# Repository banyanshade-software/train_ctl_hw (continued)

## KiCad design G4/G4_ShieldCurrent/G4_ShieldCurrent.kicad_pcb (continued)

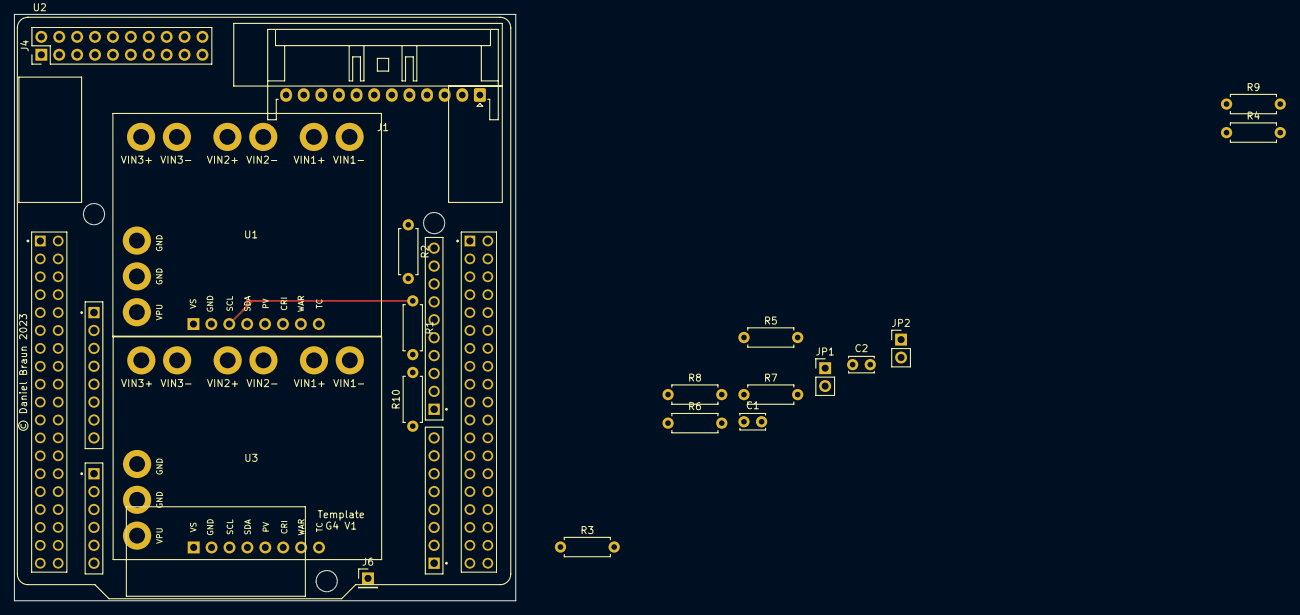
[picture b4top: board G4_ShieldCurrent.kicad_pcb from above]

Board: 2 copper layers, 71.1 x 83.2 mm, 20 parts (0 on the bottom side), 27 nets.

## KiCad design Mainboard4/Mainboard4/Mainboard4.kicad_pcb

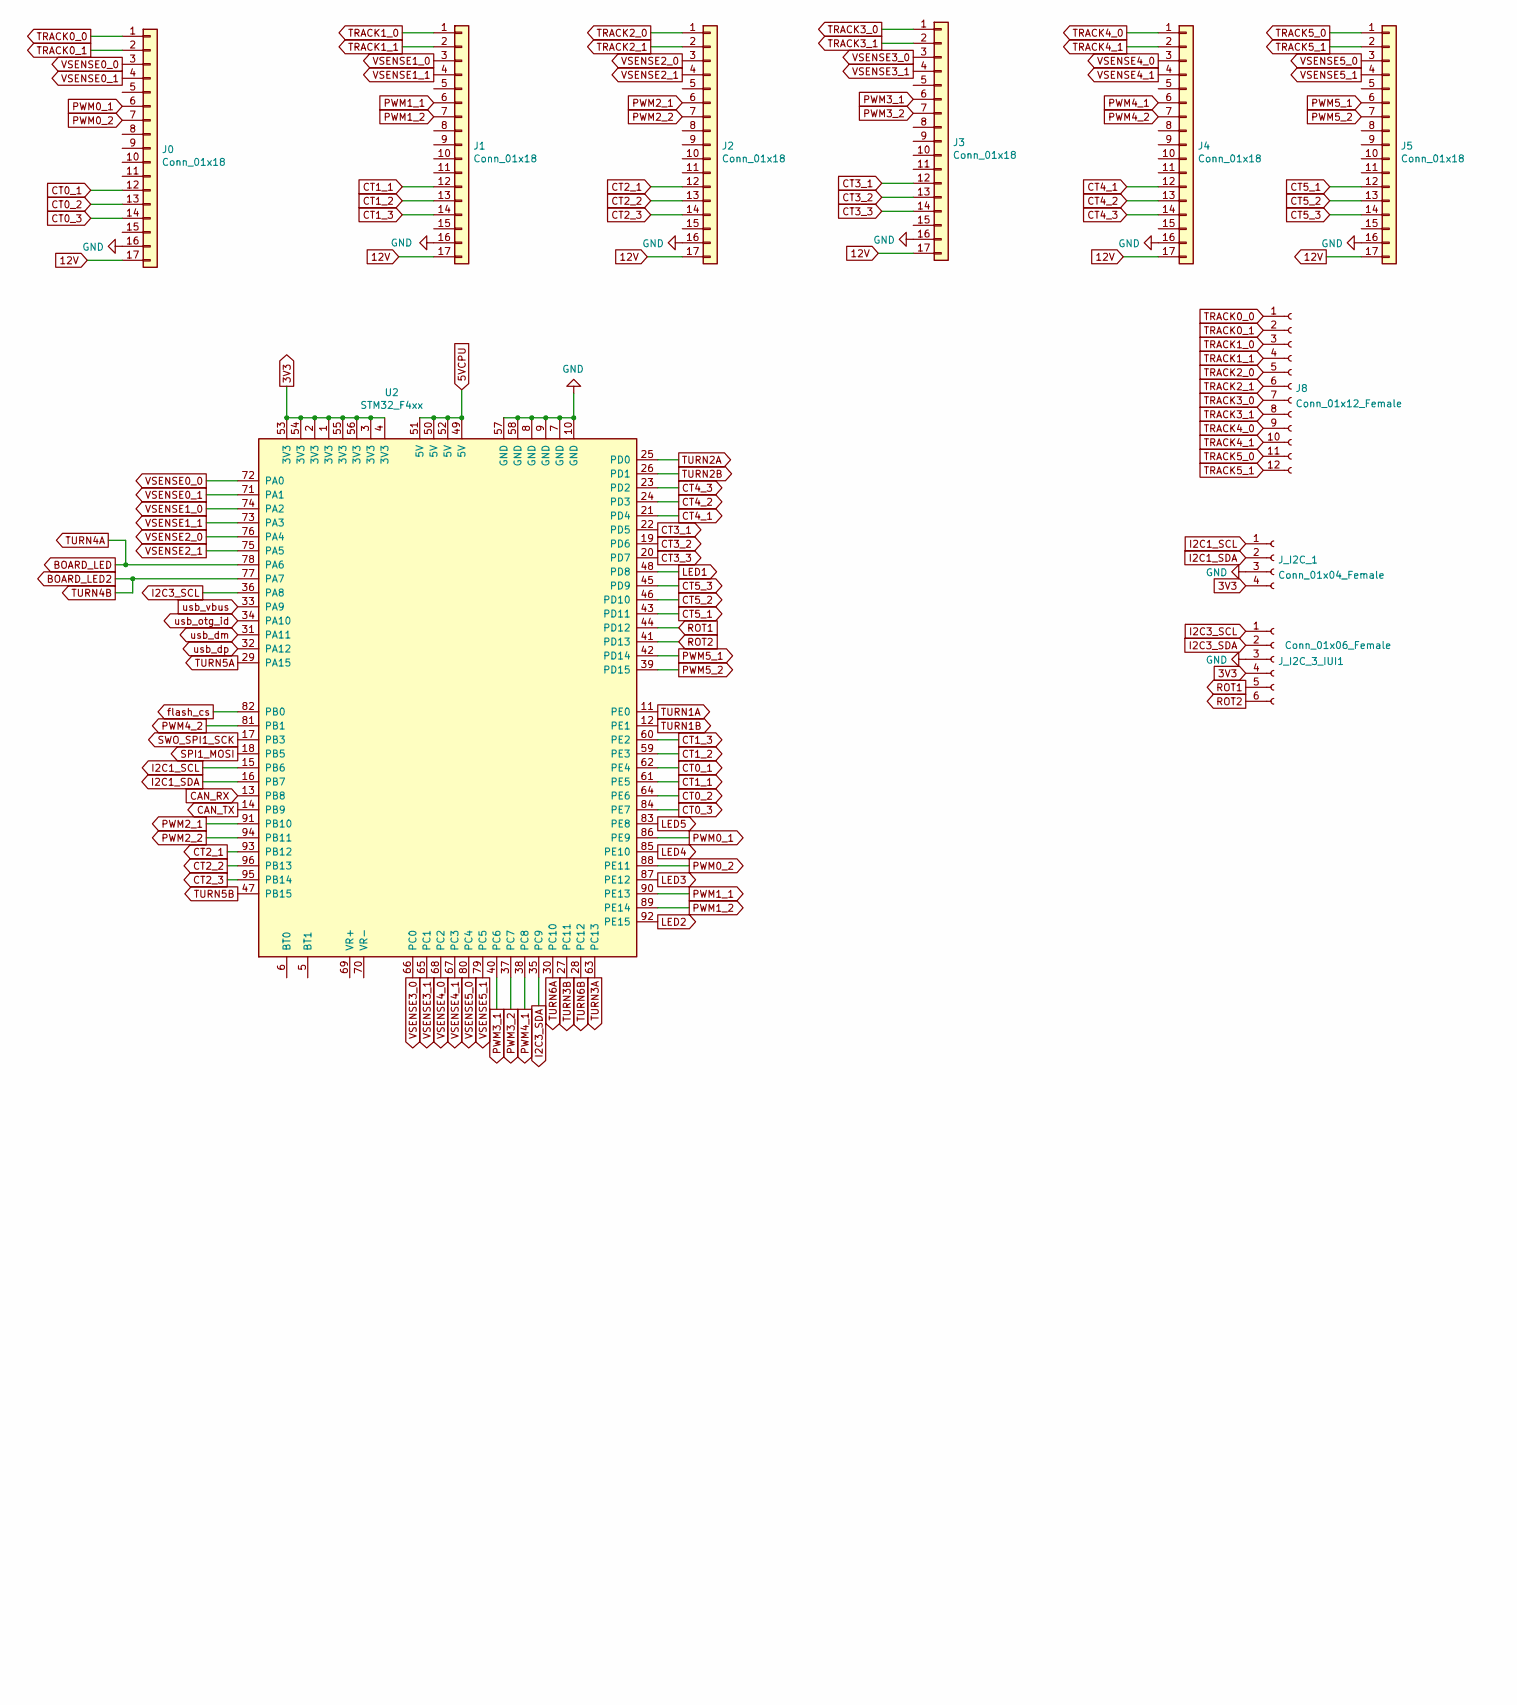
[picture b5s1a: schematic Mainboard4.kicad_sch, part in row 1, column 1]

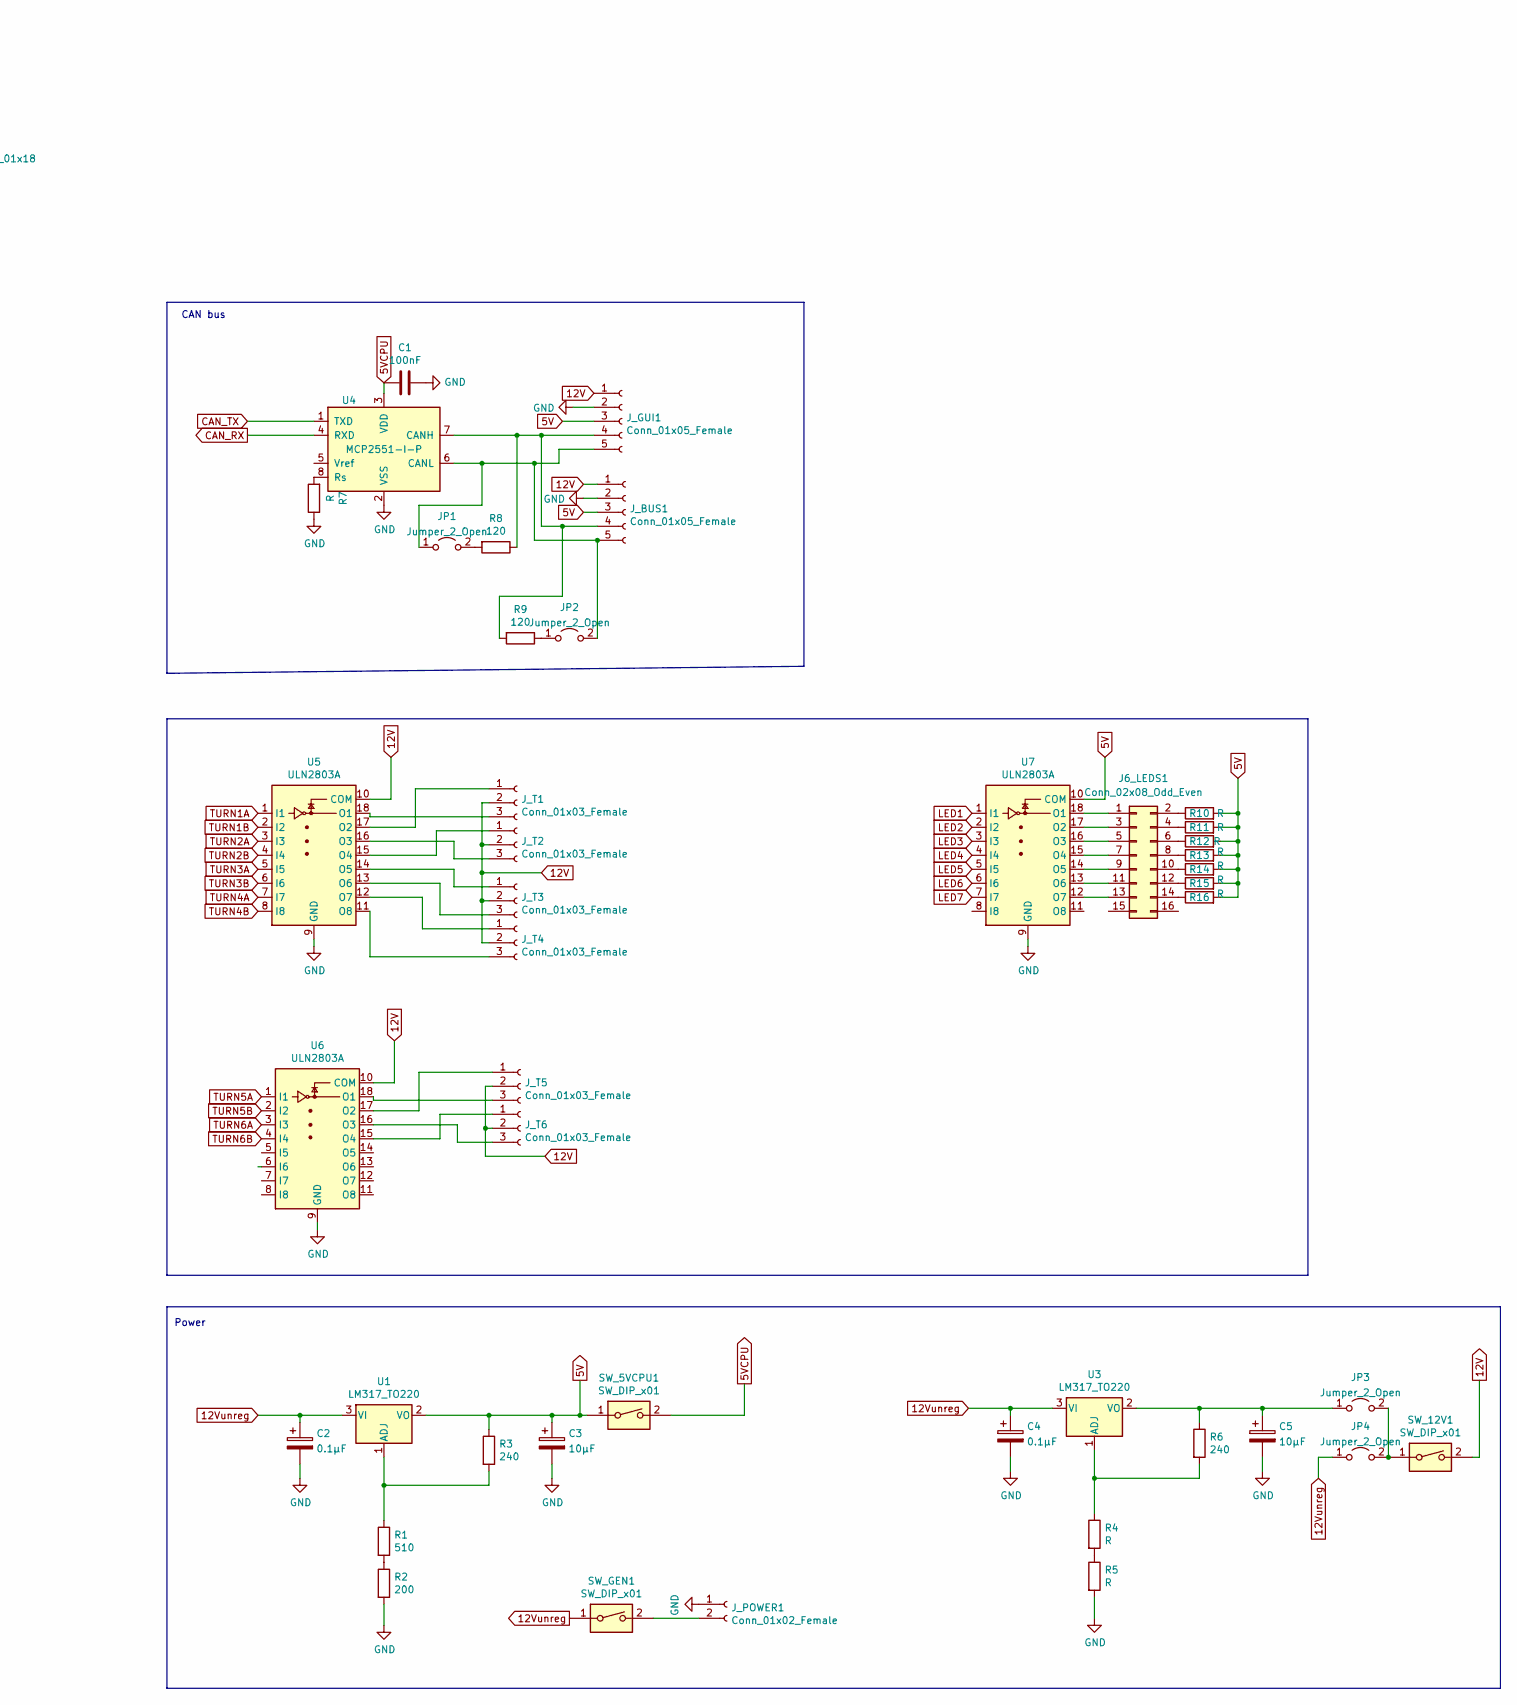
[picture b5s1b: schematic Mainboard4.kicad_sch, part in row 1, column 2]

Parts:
C1: 100nF; C_Disc_D3.4mm_W2.1mm_P2.50mm
C2, C4: 0.1µF; CP_Radial_Tantal_D5.0mm_P2.50mm
C3, C5: 10µF; CP_Radial_Tantal_D5.0mm_P2.50mm
J0, J1, J2, J3, J4, J5: Conn_01x18; PinHeader_1x17_P2.54mm_Vertical
J6_LEDS1: Conn_02x08_Odd_Even; PinHeader_2x08_P2.54mm_Vertical
J8: Conn_01x12_Female; PinHeader_1x12_P2.54mm_Vertical
JP1, JP2, JP3, JP4: Jumper_2_Open; PinHeader_1x02_P2.54mm_Vertical
J_BUS1: Conn_01x05_Female; PinHeader_1x05_P2.54mm_Vertical
J_GUI1: Conn_01x05_Female; PinHeader_1x05_P2.54mm_Vertical
J_I2C_1: Conn_01x04_Female; PinHeader_1x04_P2.54mm_Vertical
J_I2C_3_IUI1: Conn_01x06_Female; PinHeader_1x06_P2.54mm_Vertical
J_POWER1: Conn_01x02_Female; PinHeader_1x02_P2.54mm_Vertical
J_T1, J_T2, J_T3, J_T4, J_T5, J_T6: Conn_01x03_Female; PinHeader_1x03_P2.54mm_Vertical
R1: 510; R_Axial_DIN0207_L6.3mm_D2.5mm_P7.62mm_Horizontal
R2: 200; R_Axial_DIN0207_L6.3mm_D2.5mm_P7.62mm_Horizontal
R3, R6: 240; R_Axial_DIN0207_L6.3mm_D2.5mm_P7.62mm_Horizontal
R4, R5, R7, R10, R11, R12, R13, R14, R15, R16: R; R_Axial_DIN0207_L6.3mm_D2.5mm_P7.62mm_Horizontal
R8, R9: 120; R_Axial_DIN0207_L6.3mm_D2.5mm_P7.62mm_Horizontal
SW_5VCPU1, SW_12V1: SW_DIP_x01; PinHeader_1x02_P2.54mm_Vertical
SW_GEN1: SW_DIP_x01; PinHeader_1x02_P2.54mm_Vertical
U1, U3: LM317_TO220; TO-220-3_Vertical
U2: STM32_F4xx; STM32_F4XXrev
U4: MCP2551-I-P; DIP-8_W7.62mm
U5, U6, U7: ULN2803A; DIP-18_W7.62mm

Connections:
3V3: J_I2C_1.4, J_I2C_3_IUI1.4, U2.1 (3V3), U2.2 (3V3), U2.3 (3V3), U2.4 (3V3), U2.53 (3V3), U2.54 (3V3), U2.55 (3V3), U2.56 (3V3)
5V: C3.1, J_BUS1.3, J_GUI1.3, R3.1, R10.2, R11.2, R12.2, R13.2, R14.2, R15.2, R16.2, SW_5VCPU1.1, U1.2 (VO), U7.10 (COM)
5VCPU: C1.2, SW_5VCPU1.2, U2.49 (5V), U2.50 (5V), U2.51 (5V), U2.52 (5V), U4.3 (VDD)
12V: J0.17, J1.17, J2.17, J3.17, J4.17, J5.17, J_BUS1.1, J_GUI1.1, J_T1.2, J_T2.2, J_T3.2, J_T4.2, J_T5.2, J_T6.2, SW_12V1.2, U5.10 (COM), U6.10 (COM)
12Vunreg: C2.1, C4.1, JP4.1 (A), SW_GEN1.1, U1.3 (VI), U3.3 (VI)
BOARD_LED: U2.78 (PA6), U5.7 (I7)
BOARD_LED2: U2.77 (PA7), U5.8 (I8)
CAN_RX: U2.13 (PB8), U4.4 (RXD)
CAN_TX: U2.14 (PB9), U4.1 (TXD)
CT0_1: J0.12, U2.62 (PE4)
CT0_2: J0.13, U2.64 (PE6)
CT0_3: J0.14, U2.84 (PE7)
CT1_1: J1.12, U2.61 (PE5)
CT1_2: J1.13, U2.59 (PE3)
CT1_3: J1.14, U2.60 (PE2)
CT2_1: J2.12, U2.93 (PB12)
CT2_2: J2.13, U2.96 (PB13)
CT2_3: J2.14, U2.95 (PB14)
CT3_1: J3.12, U2.22 (PD5)
CT3_2: J3.13, U2.19 (PD6)
CT3_3: J3.14, U2.20 (PD7)
CT4_1: J4.12, U2.21 (PD4)
CT4_2: J4.13, U2.24 (PD3)
CT4_3: J4.14, U2.23 (PD2)
CT5_1: J5.12, U2.43 (PD11)
CT5_2: J5.13, U2.46 (PD10)
CT5_3: J5.14, U2.45 (PD9)
GND: C1.1, C2.2, C3.2, C4.2, C5.2, J0.16, J1.16, J2.16, J3.16, J4.16, J5.16, J_BUS1.2, J_GUI1.2, J_I2C_1.3, J_I2C_3_IUI1.3, J_POWER1.1, R2.2, R5.2, R7.1, U2.7 (GND), U2.8 (GND), U2.9 (GND), U2.10 (GND), U2.57 (GND), U2.58 (GND), U4.2 (VSS), U5.9 (GND), U6.9 (GND), U7.9 (GND)
I2C1_SCL: J_I2C_1.1, U2.15 (PB6)
I2C1_SDA: J_I2C_1.2, U2.16 (PB7)
I2C3_SCL: J_I2C_3_IUI1.1, U2.36 (PA8)
I2C3_SDA: J_I2C_3_IUI1.2, U2.35 (PC9)
LED1: U2.48 (PD8), U7.1 (I1)
LED2: U2.92 (PE15), U7.2 (I2)
LED3: U2.87 (PE12), U7.3 (I3)
LED4: U2.85 (PE10), U7.4 (I4)
LED5: U2.83 (PE8), U7.5 (I5)
LED6: U7.6 (I6)
LED7: U7.7 (I7)
unnamed: C5.1, JP3.1 (A), R6.1, U3.2 (VO)
unnamed: J6_LEDS1.1, U7.18 (O1)
unnamed: J6_LEDS1.2, R10.1
unnamed: J6_LEDS1.3, U7.17 (O2)
unnamed: J6_LEDS1.4, R11.1
unnamed: J6_LEDS1.5, U7.16 (O3)
unnamed: J6_LEDS1.6, R12.1
unnamed: J6_LEDS1.7, U7.15 (O4)
unnamed: J6_LEDS1.8, R13.1
unnamed: J6_LEDS1.9, U7.14 (O5)
unnamed: J6_LEDS1.10, R14.1
unnamed: J6_LEDS1.11, U7.13 (O6)
unnamed: J6_LEDS1.12, R15.1
unnamed: J6_LEDS1.13, U7.12 (O7)
unnamed: J6_LEDS1.14, R16.1
unnamed: JP1.1 (A), JP2.2 (B), J_BUS1.5, J_GUI1.5, U4.6 (CANL)
unnamed: JP1.2 (B), R8.2
unnamed: JP2.1 (A), R9.1
unnamed: JP3.2 (B), JP4.2 (B), SW_12V1.1
unnamed: J_BUS1.4, J_GUI1.4, R8.1, R9.2, U4.7 (CANH)
unnamed: J_POWER1.2, SW_GEN1.2
unnamed: J_T1.1, U5.17 (O2)
unnamed: J_T1.3, U5.18 (O1)
unnamed: J_T2.1, U5.15 (O4)
unnamed: J_T2.3, U5.16 (O3)
unnamed: J_T3.1, U5.14 (O5)
unnamed: J_T3.3, U5.13 (O6)
unnamed: J_T4.1, U5.12 (O7)
unnamed: J_T4.3, U5.11 (O8)
unnamed: J_T5.1, U6.17 (O2)
unnamed: J_T5.3, U6.18 (O1)
unnamed: J_T6.1, U6.15 (O4)
unnamed: J_T6.3, U6.16 (O3)
unnamed: R1.1, R3.2, U1.1 (ADJ)
unnamed: R1.2, R2.1
unnamed: R4.1, R6.2, U3.1 (ADJ)
unnamed: R4.2, R5.1
unnamed: R7.2, U4.8 (Rs)
PWM0_1: J0.6, U2.86 (PE9)
PWM0_2: J0.7, U2.88 (PE11)
PWM1_1: J1.6, U2.90 (PE13)
PWM1_2: J1.7, U2.89 (PE14)
PWM2_1: J2.6, U2.91 (PB10)
PWM2_2: J2.7, U2.94 (PB11)
PWM3_1: J3.6, U2.40 (PC6)
PWM3_2: J3.7, U2.37 (PC7)
PWM4_1: J4.6, U2.38 (PC8)
PWM4_2: J4.7, U2.81 (PB1)
PWM5_1: J5.6, U2.42 (PD14)
PWM5_2: J5.7, U2.39 (PD15)
ROT1: J_I2C_3_IUI1.5, U2.44 (PD12)
ROT2: J_I2C_3_IUI1.6, U2.41 (PD13)
SPI1_MOSI: U2.18 (PB5)
SWO_SPI1_SCK: U2.17 (PB3)
TRACK0_0: J0.1, J8.1
TRACK0_1: J0.2, J8.2
TRACK1_0: J1.1, J8.3
TRACK1_1: J1.2, J8.4
TRACK2_0: J2.1, J8.5
TRACK2_1: J2.2, J8.6
TRACK3_0: J3.1, J8.7
TRACK3_1: J3.2, J8.8
TRACK4_0: J4.1, J8.9
TRACK4_1: J4.2, J8.10
TRACK5_0: J5.1, J8.11
TRACK5_1: J5.2, J8.12
TURN1A: U2.11 (PE0), U5.1 (I1)
TURN1B: U2.12 (PE1), U5.2 (I2)
TURN2A: U2.25 (PD0), U5.3 (I3)
TURN2B: U2.26 (PD1), U5.4 (I4)
TURN3A: U2.63 (PC13), U5.5 (I5)
TURN3B: U2.27 (PC11), U5.6 (I6)
TURN5A: U2.29 (PA15), U6.1 (I1)
TURN5B: U2.47 (PB15), U6.2 (I2)
TURN6A: U2.30 (PC10), U6.3 (I3)
TURN6B: U2.28 (PC12), U6.4 (I4)
VSENSE0_0: J0.3, U2.72 (PA0)
VSENSE0_1: J0.4, U2.71 (PA1)
VSENSE1_0: J1.3, U2.74 (PA2)
VSENSE1_1: J1.4, U2.73 (PA3)
VSENSE2_0: J2.3, U2.76 (PA4)
VSENSE2_1: J2.4, U2.75 (PA5)
VSENSE3_0: J3.3, U2.66 (PC0)
VSENSE3_1: J3.4, U2.65 (PC1)
VSENSE4_0: J4.3, U2.68 (PC2)
VSENSE4_1: J4.4, U2.67 (PC3)
VSENSE5_0: J5.3, U2.80 (PC4)
VSENSE5_1: J5.4, U2.79 (PC5)
flash_cs: U2.82 (PB0)
usb_dm: U2.31 (PA11)
usb_dp: U2.32 (PA12)
usb_otg_id: U2.34 (PA10)
usb_vbus: U2.33 (PA9)

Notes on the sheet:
CAN bus
Power

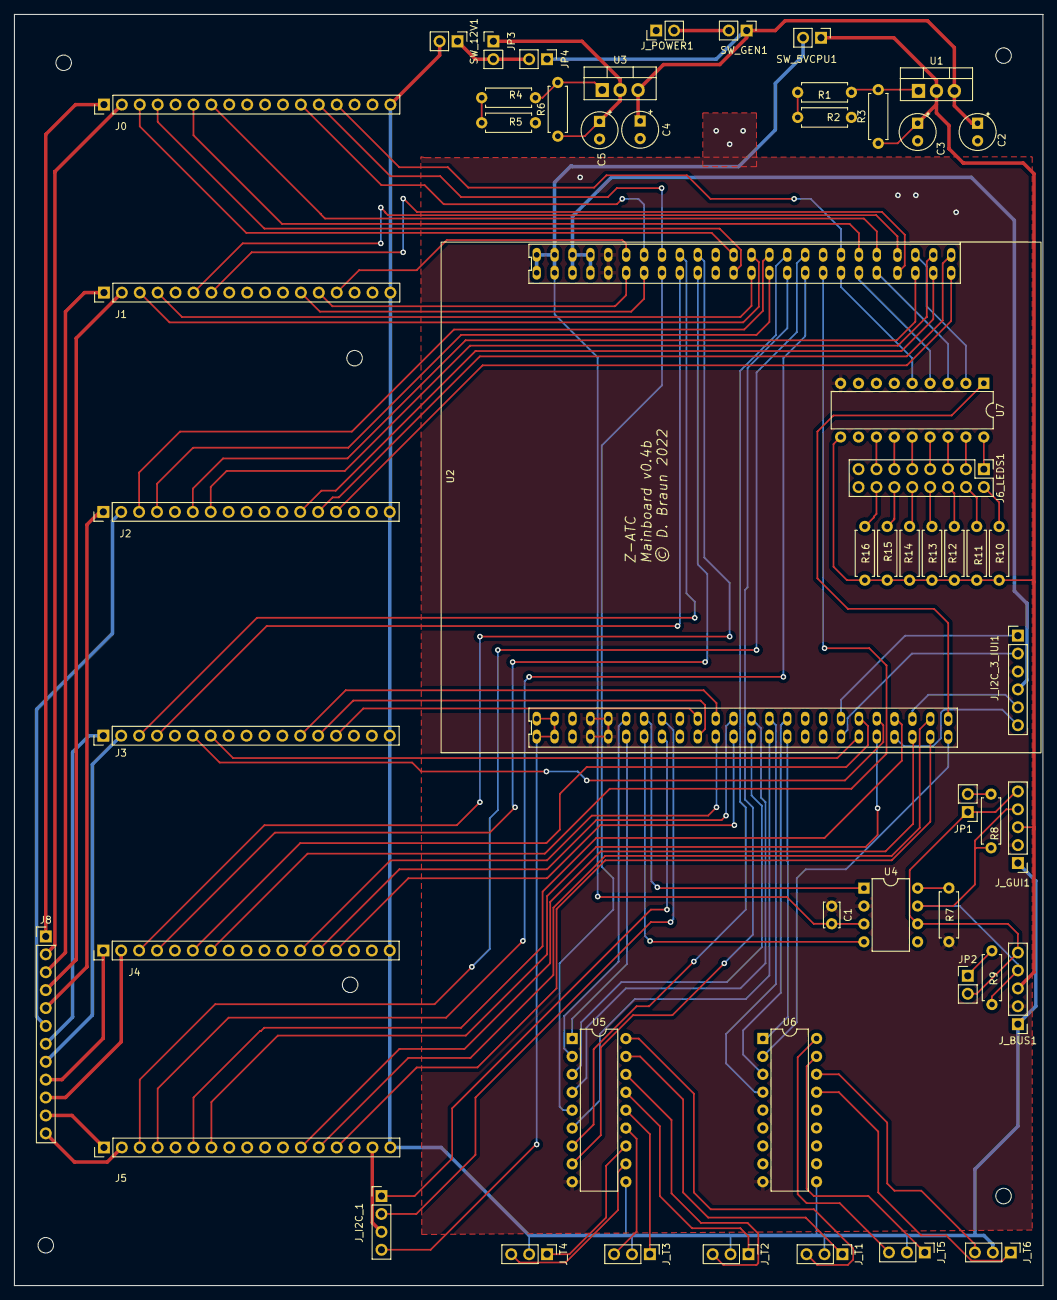
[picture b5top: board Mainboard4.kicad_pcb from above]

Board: 2 copper layers, 145.9 x 180.3 mm, 54 parts (0 on the bottom side), 123 nets.

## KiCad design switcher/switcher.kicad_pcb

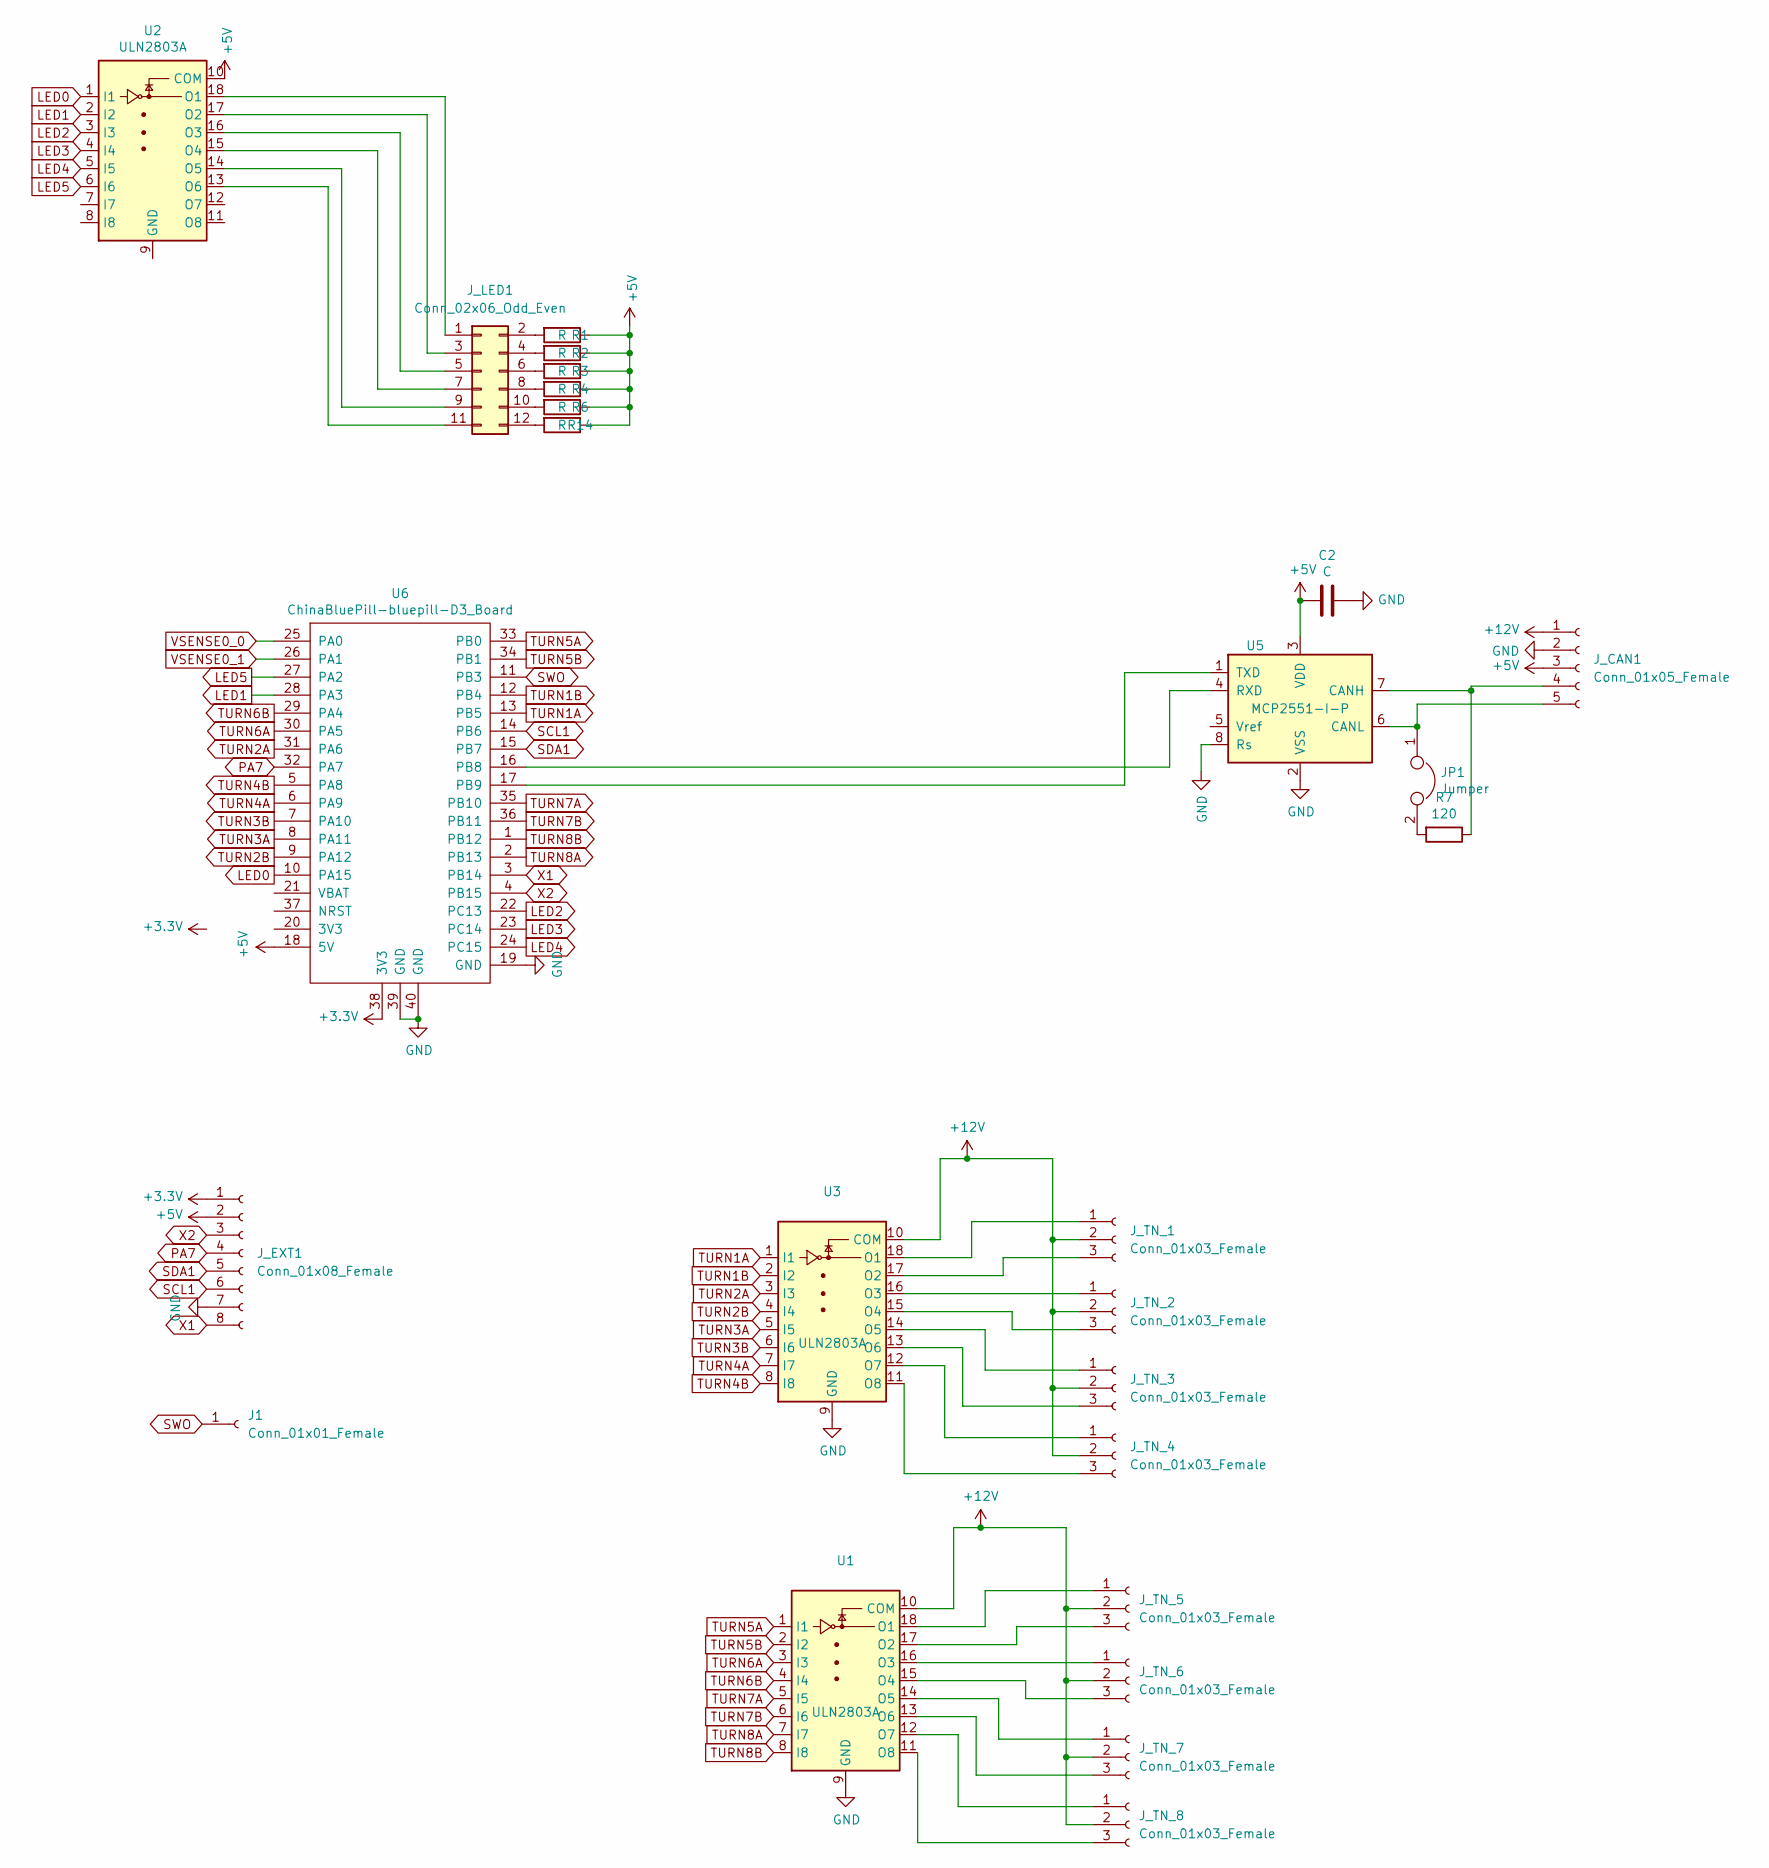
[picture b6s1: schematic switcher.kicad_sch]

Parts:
C2: C; C_Disc_D3.4mm_W2.1mm_P2.50mm
J1: Conn_01x01_Female; PinHeader_1x01_P2.54mm_Vertical
JP1: Jumper; PinHeader_1x02_P2.54mm_Vertical
J_CAN1: Conn_01x05_Female; PinHeader_1x05_P2.54mm_Vertical
J_EXT1: Conn_01x08_Female; PinHeader_1x08_P2.54mm_Vertical
J_LED1: Conn_02x06_Odd_Even; PinHeader_2x06_P2.54mm_Vertical
J_TN_1, J_TN_2, J_TN_3, J_TN_4, J_TN_5, J_TN_6, J_TN_7, J_TN_8: Conn_01x03_Female; PinHeader_1x03_P2.54mm_Vertical
R1, R2, R3, R4, R6, R14: R; R_Axial_DIN0207_L6.3mm_D2.5mm_P7.62mm_Horizontal
R7: 120; R_Axial_DIN0207_L6.3mm_D2.5mm_P7.62mm_Horizontal
U1, U2, U3: ULN2803A; DIP-18_W7.62mm
U5: MCP2551-I-P; DIP-8_W7.62mm
U6: ChinaBluePill-bluepill-D3_Board; BluePill_STM32F103C

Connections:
+3V3: J_EXT1.1, U6.38 (3V3)
+5V: C2.2, J_CAN1.3, J_EXT1.2, R1.1, R2.1, R3.1, R4.1, R6.1, R14.1, U2.10 (COM), U5.3 (VDD), U6.18 (5V)
+12V: J_CAN1.1, J_TN_1.2, J_TN_2.2, J_TN_3.2, J_TN_4.2, J_TN_5.2, J_TN_6.2, J_TN_7.2, J_TN_8.2, U1.10 (COM), U3.10 (COM)
GND: C2.1, J_CAN1.2, J_EXT1.7, U1.9 (GND), U3.9 (GND), U5.2 (VSS), U5.8 (Rs), U6.19 (GND), U6.39 (GND), U6.40 (GND)
LED0: U2.1 (I1), U6.10 (PA15)
LED1: U2.2 (I2), U6.28 (PA3)
LED2: U2.3 (I3), U6.22 (PC13)
LED3: U2.4 (I4), U6.23 (PC14)
LED4: U2.5 (I5), U6.24 (PC15)
LED5: U2.6 (I6), U6.27 (PA2)
unnamed: JP1.1, J_CAN1.5, U5.6 (CANL)
unnamed: JP1.2, R7.2
unnamed: J_CAN1.4, R7.1, U5.7 (CANH)
unnamed: J_TN_1.1, U3.18 (O1)
unnamed: J_TN_1.3, U3.17 (O2)
unnamed: J_TN_2.1, U3.16 (O3)
unnamed: J_TN_2.3, U3.15 (O4)
unnamed: J_TN_3.1, U3.14 (O5)
unnamed: J_TN_3.3, U3.13 (O6)
unnamed: J_TN_5.1, U1.18 (O1)
unnamed: J_TN_5.3, U1.17 (O2)
unnamed: J_TN_6.1, U1.16 (O3)
unnamed: J_TN_6.3, U1.15 (O4)
unnamed: J_TN_7.1, U1.14 (O5)
unnamed: J_TN_7.3, U1.13 (O6)
unnamed: J_TN_8.1, U1.12 (O7)
unnamed: J_TN_8.3, U1.11 (O8)
unnamed: J_LED1.2, R1.2
unnamed: J_LED1.4, R2.2
unnamed: J_LED1.6, R3.2
unnamed: J_LED1.8, R4.2
unnamed: J_LED1.10, R6.2
unnamed: J_LED1.12, R14.2
unnamed: J_LED1.11, U2.13 (O6)
unnamed: J_LED1.9, U2.14 (O5)
unnamed: J_LED1.7, U2.15 (O4)
unnamed: J_LED1.5, U2.16 (O3)
unnamed: J_LED1.3, U2.17 (O2)
unnamed: J_LED1.1, U2.18 (O1)
unnamed: J_TN_4.3, U3.11 (O8)
unnamed: J_TN_4.1, U3.12 (O7)
unnamed: U5.1 (TXD), U6.17 (PB9)
unnamed: U5.4 (RXD), U6.16 (PB8)
PA7: J_EXT1.4, U6.32 (PA7)
SCL1: J_EXT1.6, U6.14 (PB6)
SDA1: J_EXT1.5, U6.15 (PB7)
SWO: J1.1, U6.11 (PB3)
TURN1A: U3.1 (I1), U6.13 (PB5)
TURN1B: U3.2 (I2), U6.12 (PB4)
TURN2A: U3.3 (I3), U6.31 (PA6)
TURN2B: U3.4 (I4), U6.9 (PA12)
TURN3A: U3.5 (I5), U6.8 (PA11)
TURN3B: U3.6 (I6), U6.7 (PA10)
TURN4A: U3.7 (I7), U6.6 (PA9)
TURN4B: U3.8 (I8), U6.5 (PA8)
TURN5A: U1.1 (I1), U6.33 (PB0)
TURN5B: U1.2 (I2), U6.34 (PB1)
TURN6A: U1.3 (I3), U6.30 (PA5)
TURN6B: U1.4 (I4), U6.29 (PA4)
TURN7A: U1.5 (I5), U6.35 (PB10)
TURN7B: U1.6 (I6), U6.36 (PB11)
TURN8A: U1.7 (I7), U6.2 (PB13)
TURN8B: U1.8 (I8), U6.1 (PB12)
VSENSE0_0: U6.25 (PA0)
VSENSE0_1: U6.26 (PA1)
X1: J_EXT1.8, U6.3 (PB14)
X2: J_EXT1.3, U6.4 (PB15)

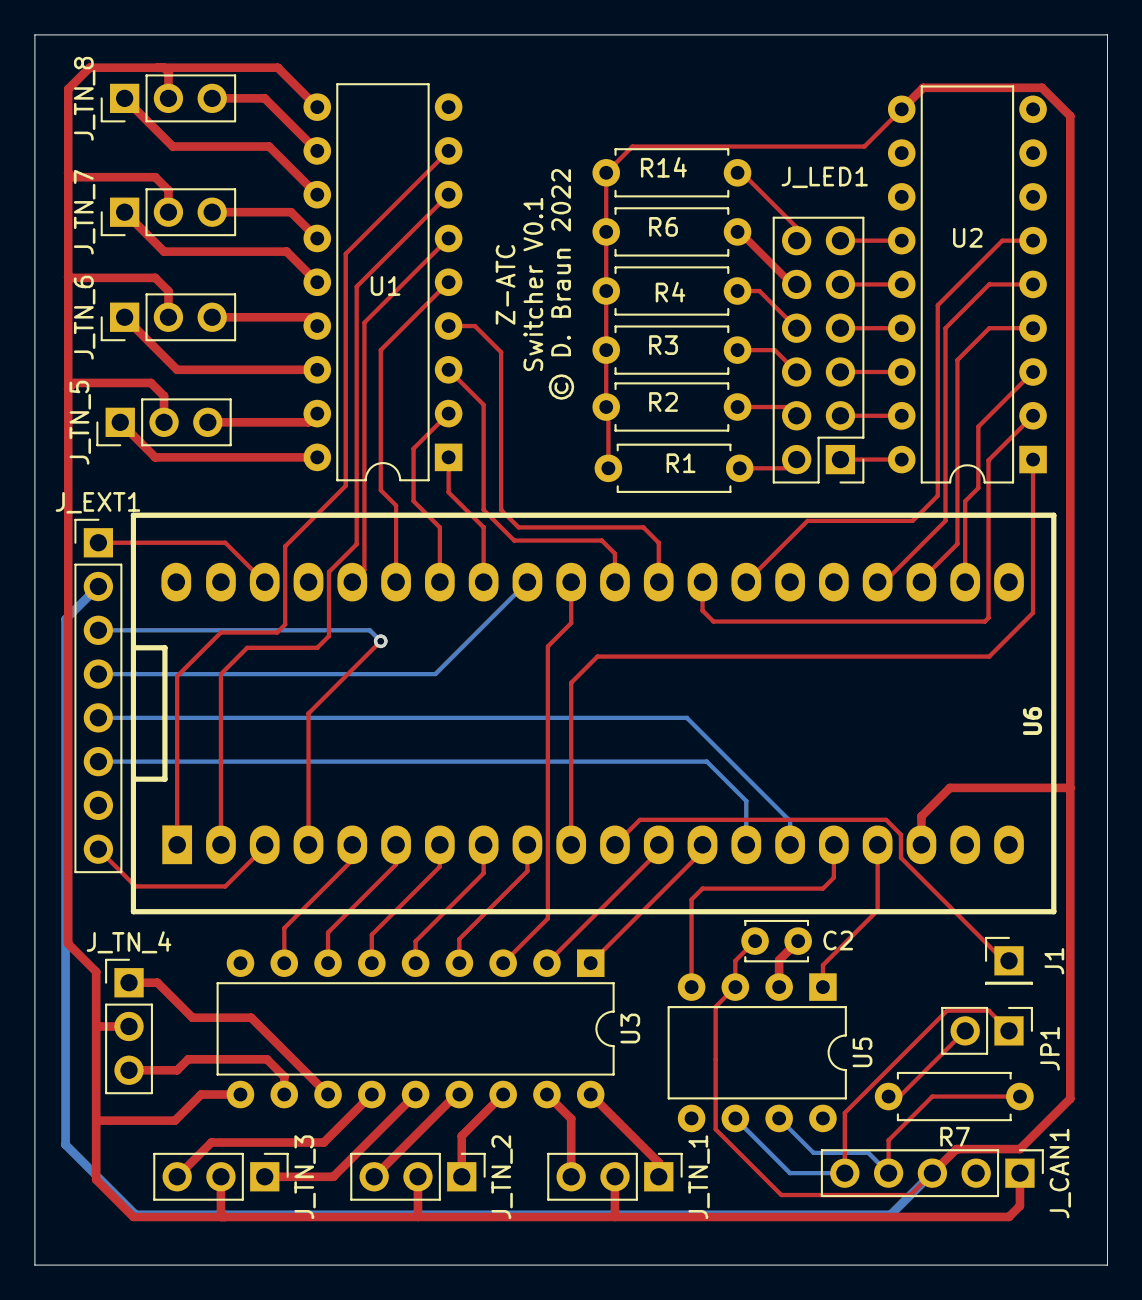
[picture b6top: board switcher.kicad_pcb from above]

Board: 2 copper layers, 62.2 x 71.4 mm, 26 parts (0 on the bottom side), 65 nets.
